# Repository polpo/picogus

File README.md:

# PicoGUS

ISA sound card and CD-ROM drive emulation on the Raspberry Pi Pico's RP2040 microcontroller. PicoGUS can emulate:

* [Gravis Ultrasound (GUS)](https://en.wikipedia.org/wiki/Gravis_Ultrasound) - the primary focus of PicoGUS, hence the name
* [Sound Blaster 16](https://en.wikipedia.org/wiki/Sound_Blaster_16) (OPL3) / [Sound Blaster Pro 2](https://en.wikipedia.org/wiki/Sound_Blaster#Sound_Blaster_Pro_2,_CT1600) (OPL3) / [AdLib](https://en.wikipedia.org/wiki/Ad_Lib,_Inc.) (OPL2)
* [MPU-401 (with intelligent mode)](https://en.wikipedia.org/wiki/MPU-401) - outputs MIDI data on 3.5mm MIDI TRS connector
* [Tandy 3-voice](http://www.vgmpf.com/Wiki/index.php?title=Tandy_3_Voice)
* [CMS/Game Blaster](http://nerdlypleasures.blogspot.com/2012/10/all-you-ever-wanted-to-know-about.html)
* [Game port joystick](https://en.wikipedia.org/wiki/Game_port)
* [Panasonic/MKE CD-ROM](https://en.wikipedia.org/wiki/Panasonic_CD_interface)
* USB drive access from DOS: the drive plugged into the PicoGUS mapped to a DOS drive letter with `PGUSDFS.EXE` (see [pgusdfs/README.md](pgusdfs/README.md))

Current status: perpetual beta! See the [main wiki page](https://github.com/polpo/picogus/wiki) for current status and the [compatibility list](https://github.com/polpo/picogus/wiki/Compatibility-list) for support status of various DOS programs and other system compatibility notes. This project has a heavy demoscene focus due to the GUS's history so that's what I've concentrated on, but GUS support in games is very good to excellent.

Want to buy a PicoGUS? Fully assembled PicoGUS 2.0 sound cards are available from these sources, all of whom ship worldwide:

* [Joe's Computer Museum Shop](https://jcm-1.com/product/picogus-v2/) - in US 🇺🇸
* [Serdashop](https://www.serdashop.com/PicoGUS) - in EU 🇪🇺
* [Flamelily IT](https://shop.flamelily.co.uk/picogus) - in UK 🇬🇧

Want to make your own PicoGUS? See the [build guide](https://github.com/polpo/picogus/wiki/Building-your-PicoGUS). Note that the more DIY friendly v1.1.1 hardware has some documented issues with reset – a forthcoming v1.2 revision will fix these issues. **Important caveat**: due to the specs of the Pico, assumptions made by programs written to use the GUS, the imprecise nature of emulation, and the varying specs of retro DOS PC hardware, some things will likely never be perfect. **This is still a work in progress.**

Have a PicoGUS and want to use it? See the [configuring and using your PicoGUS guide](https://github.com/polpo/picogus/wiki/Configuring-and-using-your-PicoGUS).

Want to support PicoGUS? I have a limited number of machines to test PicoGUS in and donating either money or motherboards would be greatly appreciated and help increase the compatibility of PicoGUS.

You can donate via [PayPal](https://paypal.me/ianpolpo) or Ko-Fi: 

See/hear PicoGUS in action on YouTube:

Videos by others:

My videos:

## Open Source Credits

* [Raspberry Pi Pico C/C++ SDK](https://github.com/raspberrypi/pico-sdk)
* `pico_audio_i2s` from [pico-extras](https://github.com/raspberrypi/pico-extras)
* `stdio_async_uart` from [PicoCart64](https://github.com/kbeckmann/PicoCart64)
* `gus-x.cpp` adapted from [DOSBox-X](https://github.com/joncampbell123/dosbox-x)
* OPL/AdLib emulation from [rp2040-doom](https://github.com/kilograham/rp2040-doom) (based on [emu8950](https://github.com/digital-sound-antiques/emu8950))
* MPU-401 emulation adapted from [HardMPU](https://github.com/ab0tj/HardMPU) and [DOSBox-X](https://github.com/joncampbell123/dosbox-x)
* Tandy 3-voice emulation based on code contributed by [Aaron Giles](https://aarongiles.com/), adapted from [DREAMM](https://aarongiles.com/dreamm/) 
* CMS emulation based on code contributed by [Aaron Giles](https://aarongiles.com/), adapted from [DREAMM](https://aarongiles.com/dreamm/)
* USB support uses [TinyUSB](https://github.com/hathach/tinyusb) and [tusb_xinput](https://github.com/Ryzee119/tusb_xinput) with USB mass storage improvements by rppicomidi and wbcbz7.
* FAT drive support by [FatFS](https://elm-chan.org/fsw/ff/)

## License

The hardware portions of this repository (hw/ directory) are licensed under the CERN OHL version 2, permissive.

The software portions of this repository (sw/, pgusinit/ directories) as a collection are licensed under the GNU GPL version 2. Some files are individually dual-licensed under BSD or MIT licenses – see the license in the file headers for details.

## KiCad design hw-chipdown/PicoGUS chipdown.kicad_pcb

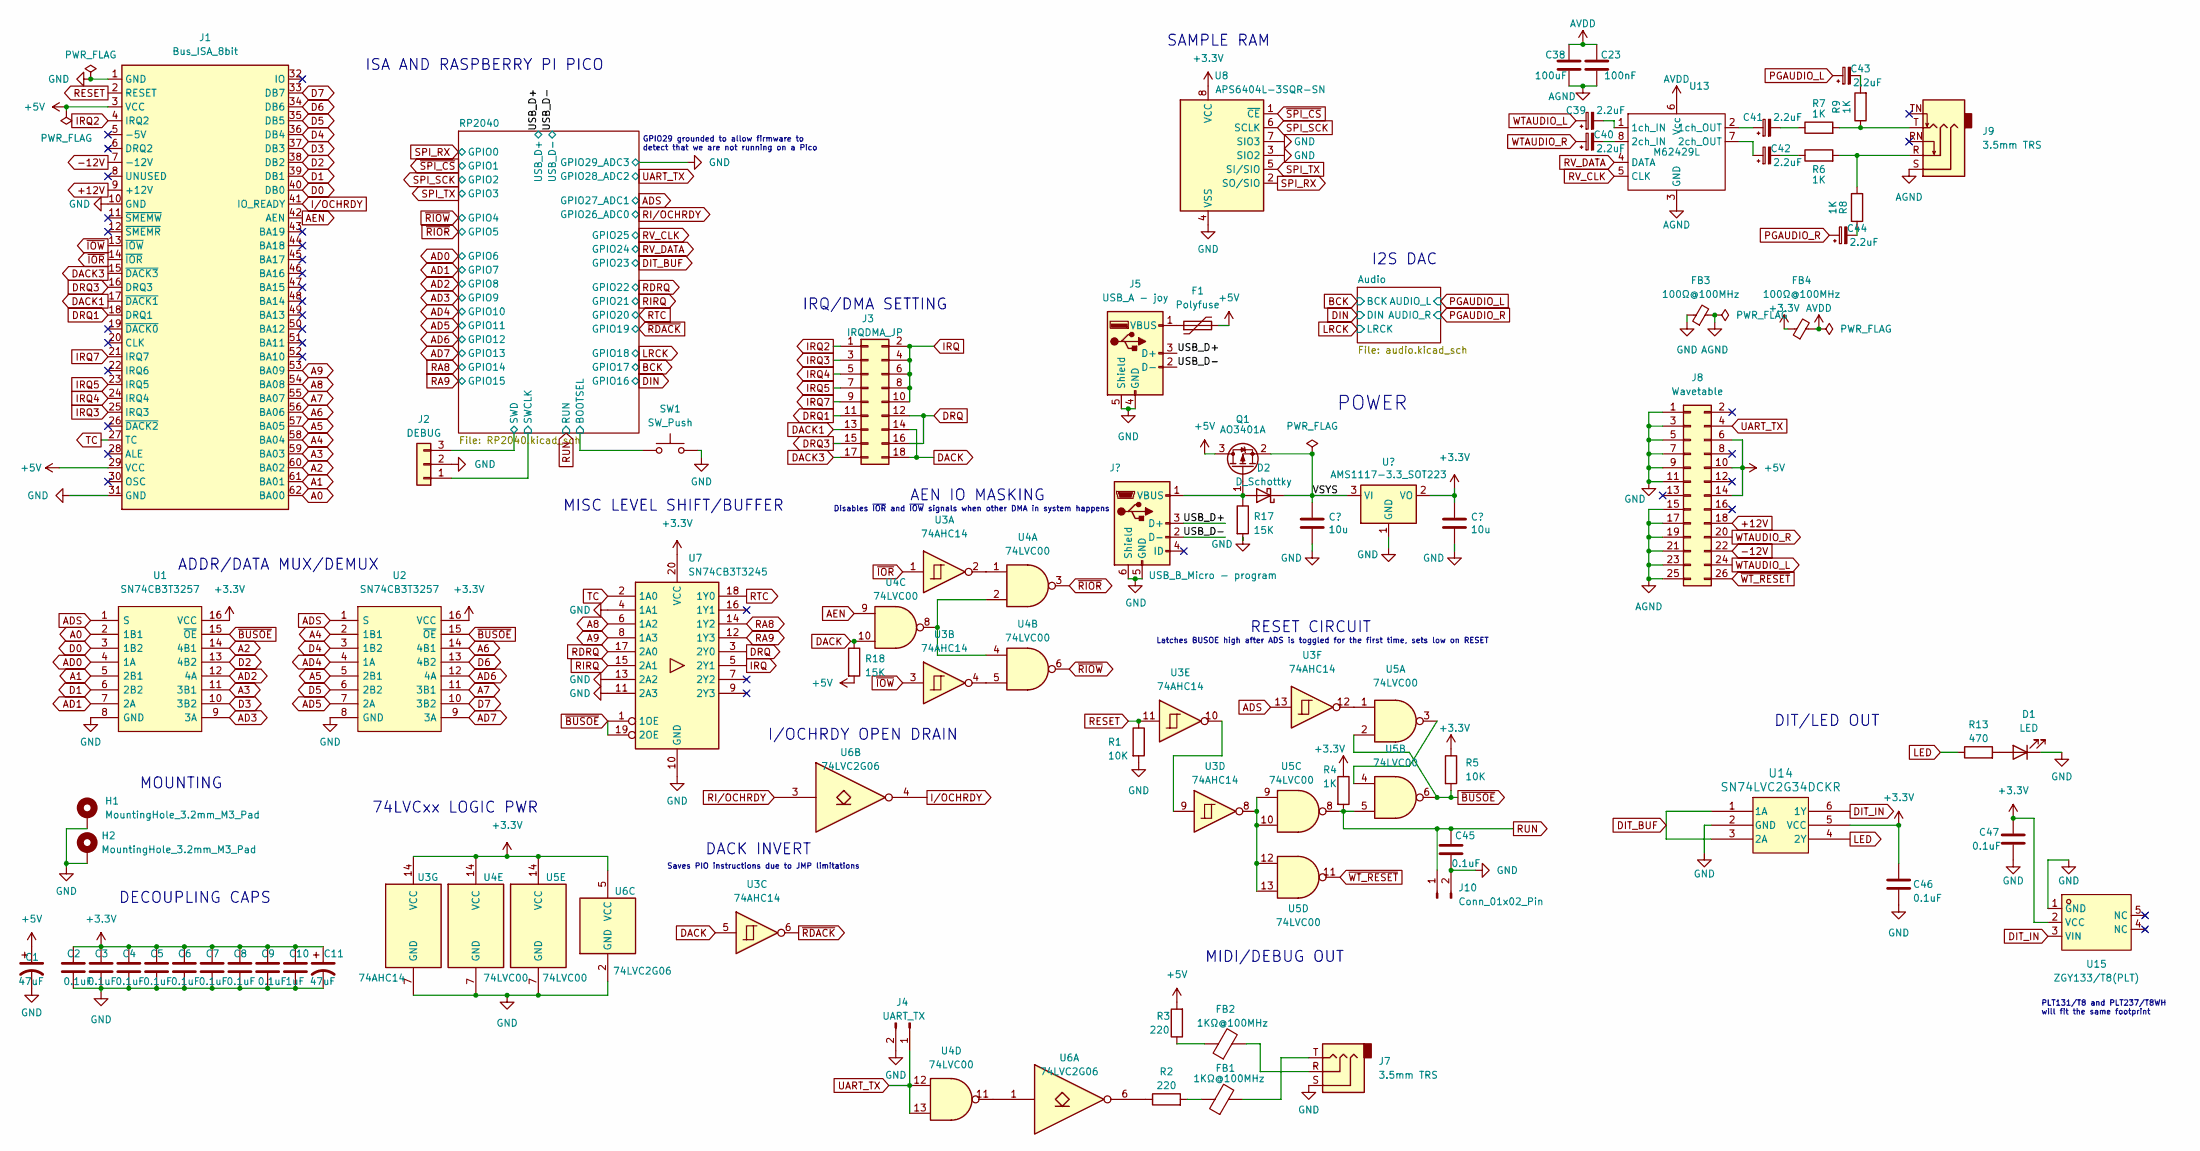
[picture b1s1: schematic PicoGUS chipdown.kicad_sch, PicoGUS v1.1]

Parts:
C1, C11: 47uF; C_1206_3216Metric
C2, C3, C4, C5, C6, C7, C8, C9, C45, C46, C47: 0.1uF; C_0402_1005Metric
C10: 1uF; C_0603_1608Metric
C12, C13: 10u; C_0805_2012Metric
C23: 100nF; C_0402_1005Metric
C38: 100uF; C_1206_3216Metric
C39, C40, C41, C42, C43, C44: 2.2uF; CP_Elec_4x5.4
D1: LED; LED_0603_1608Metric
D2: D_Schottky; D_SOD-323_HandSoldering
F1: Polyfuse; Fuse_1206_3216Metric
FB1, FB2: 1KΩ@100MHz; L_0805_2012Metric
FB3, FB4: 100Ω@100MHz; L_0805_2012Metric
H1, H2: MountingHole_3.2mm_M3_Pad
J1: Bus_ISA_8bit; BUS_PC_chamfer
J2: DEBUG; JST_SH_BM03B-SRSS-TB_1x03-1MP_P1.00mm_Vertical
J3: IRQDMA_JP; PinHeader_2x09_P2.54mm_Vertical
J4: UART_TX; PinHeader_1x02_P2.54mm_Vertical
J5: USB_A - joy; USB-A_902-131A1011D10100
J6: USB_B_Micro - program; USB-microB_U254-051T-4BH83-F1S
J7, J9: 3.5mm TRS; Jack_3.5mm_CUI_SJ1-3535NG_Horizontal
J8: Wavetable
J10: Conn_01x02_Pin; PinHeader_1x02_P2.54mm_Vertical
Q1: AO3401A; SOT-23
R1, R5: 10K; R_0402_1005Metric
R2, R3: 220; R_0805_2012Metric
R4, R6, R7, R8, R9: 1K; R_0402_1005Metric
R13: 470; R_0402_1005Metric
R17, R18: 15K; R_0402_1005Metric
SW1: SW_Push; SW_SPST_TL3305A
U1, U2: SN74CB3T3257; TSSOP-16_4.4x5mm_P0.65mm; Manufacturer_Part_Number 74FST3257DR2G; Mouser Part Number 863-74FST3257DR2G
U3: 74AHC14; TSSOP-14_4.4x5mm_P0.65mm
U4, U5: 74LVC00; TSSOP-14_4.4x5mm_P0.65mm
U6: 74LVC2G06; SOT-363_SC-70-6
U7: SN74CB3T3245; TSSOP-20_4.4x6.5mm_P0.65mm
U8: APS6404L-3SQR-SN; SOIC-8_3.9x4.9mm_P1.27mm
U9: AMS1117-3.3_SOT223; SOT-223-3_TabPin2
U13: M62429L; SOIC-8_3.9x4.9mm_P1.27mm
U14: SN74LVC2G34DCKR; SOT-363_SC-70-6
U15: ZGY133/T8(PLT); OPTO-TH_ZGY133-T8-PLT; LCSC Part C277780

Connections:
+5V: C1.1, F1.2, J1.3 (VCC), J1.29 (VCC), J8.6, J8.10, J8.14, Q1.3 (D), R3.2, R18.2
+12V: J1.9 (+12V), J8.18
-12V: J1.7 (-12V), J8.22
/RP2040/SWCLK: J2.1; also elsewhere on the board
/RP2040/SWD: J2.3; also elsewhere on the board
/RP2040/~USB_BOOT: SW1.1; also elsewhere on the board
/USB_D+: J5.3 (D+), J6.3 (D+); also elsewhere on the board
/USB_D-: J5.2 (D-), J6.2 (D-); also elsewhere on the board
/VSYS: C12.1, D2.1 (K), Q1.2 (S), U9.3 (VI)
A0: J1.62 (BA00), U1.2 (1B1)
A1: J1.61 (BA01), U1.5 (2B1)
A2: J1.60 (BA02), U1.14 (4B1)
A3: J1.59 (BA03), U1.11 (3B1)
A4: J1.58 (BA04), U2.2 (1B1)
A5: J1.57 (BA05), U2.5 (2B1)
A6: J1.56 (BA06), U2.14 (4B1)
A7: J1.55 (BA07), U2.11 (3B1)
A8: J1.54 (BA08), U7.6 (1A2)
A9: J1.53 (BA09), U7.8 (1A3)
AD0: U1.4 (1A); also elsewhere on the board
AD1: U1.7 (2A); also elsewhere on the board
AD2: U1.12 (4A); also elsewhere on the board
AD3: U1.9 (3A); also elsewhere on the board
AD4: U2.4 (1A); also elsewhere on the board
AD5: U2.7 (2A); also elsewhere on the board
AD6: U2.12 (4A); also elsewhere on the board
AD7: U2.9 (3A); also elsewhere on the board
ADS: U1.1 (S), U2.1 (S), U3.13; also elsewhere on the board
AEN: J1.42 (AEN), U4.9
AGND: C23.2, C38.2, FB3.2, J8.15, J8.17, J8.19, J8.21, J8.23, J8.25, J9.S, U13.3 (GND); also elsewhere on the board
D0: J1.40 (DB0), U1.3 (1B2)
D1: J1.39 (DB1), U1.6 (2B2)
D2: J1.38 (DB2), U1.13 (4B2)
D3: J1.37 (DB3), U1.10 (3B2)
D4: J1.36 (DB4), U2.3 (1B2)
D5: J1.35 (DB5), U2.6 (2B2)
D6: J1.34 (DB6), U2.13 (4B2)
D7: J1.33 (DB7), U2.10 (3B2)
DACK: J3.14, J3.18, R18.1, U3.5, U4.10
DACK1: J1.17 (~DACK1), J3.13
DACK3: J1.15 (~DACK3), J3.17
DIT_BUF: U14.1 (1A), U14.3 (2A); also elsewhere on the board
DIT_IN: U14.6 (1Y), U15.3 (VIN)
DRQ: J3.12, J3.16, U7.3 (2Y0)
DRQ1: J1.18 (DRQ1), J3.11
DRQ3: J1.16 (DRQ3), J3.15
GND: C1.2, C2.2, C3.2, C4.2, C5.2, C6.2, C7.2, C8.2, C9.2, C10.2, C11.2, C12.2, C13.2, C45.2, C46.2, C47.2, D1.1 (K), FB3.1, H1.1, H2.1, J1.1 (GND), J1.10 (GND), J1.31 (GND), J2.2, J4.2, J5.4 (GND), J5.5 (Shield), J6.5 (GND), J6.6 (Shield), J7.S, J8.1, J8.3, J8.5, J8.7, J8.9, J8.11, J10.2, R1.2, R17.2, SW1.2, U1.8 (GND), U2.8 (GND), U3.7 (GND), U4.7 (GND), U5.7 (GND), U6.2 (GND), U7.4 (1A1), U7.10 (GND), U7.11 (2A3), U7.13 (2A2), U8.3 (SIO2), U8.4 (VSS), U8.7 (SIO3), U9.1 (GND), U14.2 (GND), U15.1 (GND); also elsewhere on the board
IRQ: J3.2, J3.4, J3.6, J3.8, J3.10, U7.5 (2Y1)
IRQ2: J1.4 (IRQ2), J3.1
IRQ3: J1.25 (IRQ3), J3.3
IRQ4: J1.24 (IRQ4), J3.5
IRQ5: J1.23 (IRQ5), J3.7
IRQ7: J1.21 (IRQ7), J3.9
I/OCHRDY: J1.41 (IO_READY), U6.4
LED: R13.1, U14.4 (2Y)
unnamed: C41.2, R7.1
unnamed: C42.2, R6.1
unnamed: C43.2, R9.2
unnamed: C44.2, R8.2
unnamed: D1.2 (A), R13.2
unnamed: D2.2 (A), J6.1 (VBUS), Q1.1 (G), R17.1
unnamed: FB1.1, R2.2
unnamed: FB1.2, J7.T
unnamed: FB2.1, R3.1
unnamed: FB2.2, J7.R
unnamed: F1.1, J5.1 (VBUS)
unnamed: J9.R, R6.2, R8.1
unnamed: J9.T, R7.2, R9.1
unnamed: R2.1, U6.6
unnamed: U3.2, U4.1
unnamed: U3.4, U4.5
unnamed: U3.8, U5.9, U5.10, U5.12, U5.13
unnamed: U3.9, U3.10
unnamed: U3.12, U5.1
unnamed: U4.2, U4.4, U4.8
unnamed: U4.11, U6.1
unnamed: U5.3, U5.4
unnamed: C39.2, U13.1 (1ch_IN)
unnamed: C41.1, U13.2 (1ch_OUT)
unnamed: C40.2, U13.8 (2ch_IN)
unnamed: C42.1, U13.7 (2ch_OUT)
PGAUDIO_L: C43.1; also elsewhere on the board
PGAUDIO_R: C44.1; also elsewhere on the board
RA8: U7.14 (1Y2); also elsewhere on the board
RA9: U7.12 (1Y3); also elsewhere on the board
RDRQ: U7.17 (2A0); also elsewhere on the board
RESET: J1.2 (RESET), R1.1, U3.11
RIRQ: U7.15 (2A1); also elsewhere on the board
RI/OCHRDY: U6.3; also elsewhere on the board
RTC: U7.18 (1Y0); also elsewhere on the board
RUN: C45.1, J10.1, R4.2, U5.5, U5.8; also elsewhere on the board
RV_CLK: U13.5 (CLK); also elsewhere on the board
RV_DATA: U13.4 (DATA); also elsewhere on the board
SPI_RX: U8.2 (SO/SIO); also elsewhere on the board
SPI_SCK: U8.6 (SCLK); also elsewhere on the board
SPI_TX: U8.5 (SI/SIO); also elsewhere on the board
TC: J1.27 (TC), U7.2 (1A0)
UART_TX: J4.1, J8.4, U4.12, U4.13; also elsewhere on the board
WTAUDIO_L: C39.1, J8.24
WTAUDIO_R: C40.1, J8.20
~BUSOE: R5.2, U1.15 (~OE), U2.15 (~OE), U5.2, U5.6, U7.1 (1OE), U7.19 (2OE)
~IOR: J1.14 (~IOR), U3.1
~IOW: J1.13 (~IOW), U3.3
~RDACK: U3.6; also elsewhere on the board
~RIOR: U4.3; also elsewhere on the board
~RIOW: U4.6; also elsewhere on the board
~SPI_CS: U8.1 (~CE); also elsewhere on the board
~WT_RESET: J8.26, U5.11

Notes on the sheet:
Saves PIO instructions due to JMP limitations
DECOUPLING CAPS
GPIO29 grounded to allow firmware to detect that we are not running on a Pico
I2S DAC
Disables ~{IOR} and ~{IOW} signals when other DMA in system happens
Latches BUSOE high after ADS is toggled for the first time, sets low on RESET
MIDI/DEBUG OUT
MOUNTING
MISC LEVEL SHIFT/BUFFER
IRQ/DMA SETTING
DIT/LED OUT
DACK INVERT
ADDR/DATA MUX/DEMUX
SAMPLE RAM
PLT131/T8 and PLT237/T8WH will fit the same footprint
AEN IO MASKING
ISA AND RASPBERRY PI PICO
POWER
RESET CIRCUIT
I/OCHRDY OPEN DRAIN
74LVCxx LOGIC PWR

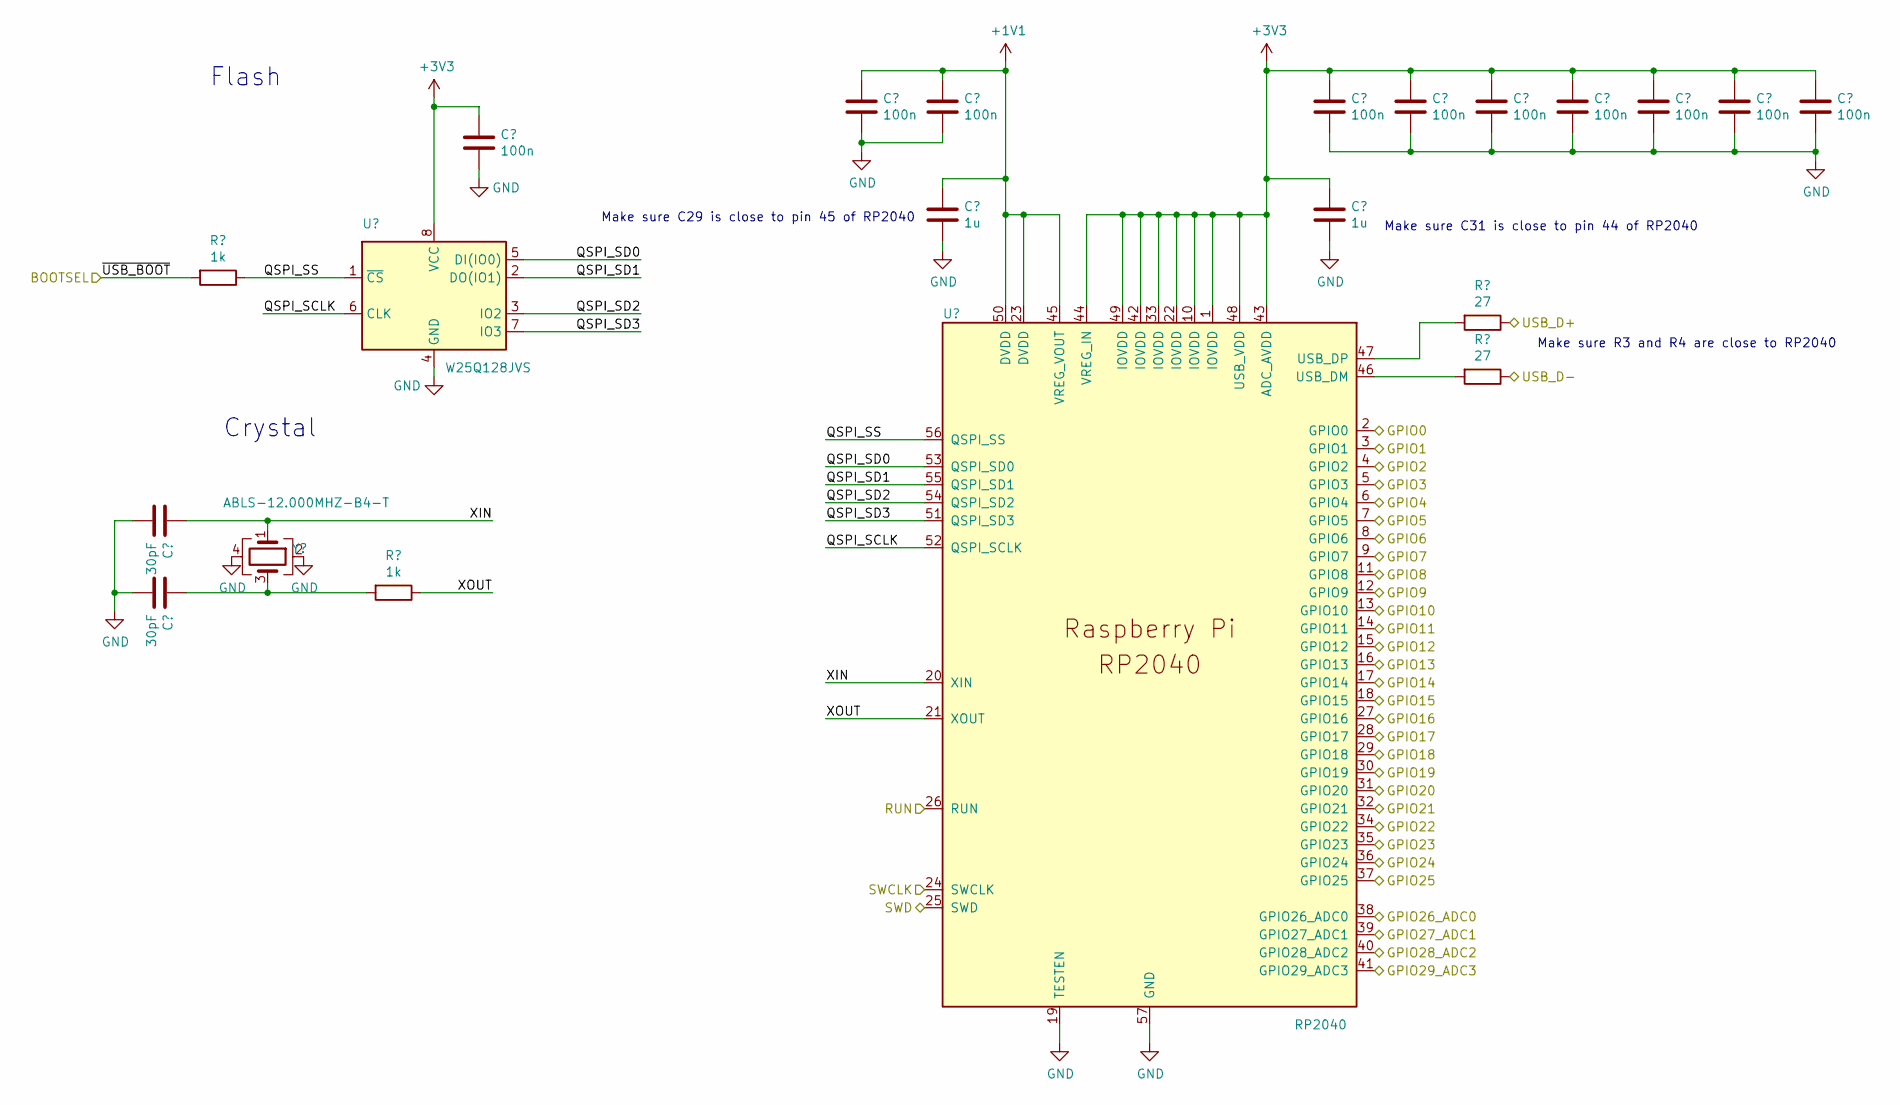
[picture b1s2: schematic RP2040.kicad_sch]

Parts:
C24, C25: 30pF; C_0402_1005Metric
C26, C27, C28, C30, C32, C33, C34, C35, C36, C37: 100n; C_0402_1005Metric
C29, C31: 1u; C_0402_1005Metric
R12, R14: 1k; C_0402_1005Metric
R15, R16: 27; C_0402_1005Metric
U11: W25Q128JVS; SOIC-8_5.23x5.23mm_P1.27mm
U12: RP2040; QFN-56-1EP_7x7mm_P0.4mm_EP3.2x3.2mm_ThermalVias
Y1: ABLS-12.000MHZ-B4-T; Crystal_SMD_3225-4Pin_3.2x2.5mm

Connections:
+1V1: C27.1, C28.1, C29.1, U12.23 (DVDD), U12.45 (VREG_VOUT), U12.50 (DVDD)
/RP2040/QSPI_SCLK: U11.6 (CLK), U12.52 (QSPI_SCLK)
/RP2040/QSPI_SD0: U11.5 (DI(IO0)), U12.53 (QSPI_SD0)
/RP2040/QSPI_SD1: U11.2 (DO(IO1)), U12.55 (QSPI_SD1)
/RP2040/QSPI_SD2: U11.3 (IO2), U12.54 (QSPI_SD2)
/RP2040/QSPI_SD3: U11.7 (IO3), U12.51 (QSPI_SD3)
/RP2040/QSPI_SS: R12.1, U11.1 (~CS), U12.56 (QSPI_SS)
/RP2040/SWCLK: U12.24 (SWCLK); also elsewhere on the board
/RP2040/SWD: U12.25 (SWD); also elsewhere on the board
/RP2040/XIN: C24.1, U12.20 (XIN), Y1.1
/RP2040/XOUT: R14.1, U12.21 (XOUT)
/RP2040/~USB_BOOT: R12.2; also elsewhere on the board
/USB_D+: R15.1; also elsewhere on the board
/USB_D-: R16.1; also elsewhere on the board
AD0: U12.8 (GPIO6); also elsewhere on the board
AD1: U12.9 (GPIO7); also elsewhere on the board
AD2: U12.11 (GPIO8); also elsewhere on the board
AD3: U12.12 (GPIO9); also elsewhere on the board
AD4: U12.13 (GPIO10); also elsewhere on the board
AD5: U12.14 (GPIO11); also elsewhere on the board
AD6: U12.15 (GPIO12); also elsewhere on the board
AD7: U12.16 (GPIO13); also elsewhere on the board
ADS: U12.39 (GPIO27_ADC1); also elsewhere on the board
BCK: U12.28 (GPIO17); also elsewhere on the board
DIN: U12.27 (GPIO16); also elsewhere on the board
DIT_BUF: U12.35 (GPIO23); also elsewhere on the board
GND: C24.2, C25.2, C26.2, C27.2, C28.2, C29.2, C30.2, C31.2, C32.2, C33.2, C34.2, C35.2, C36.2, C37.2, U11.4 (GND), U12.19 (TESTEN), U12.41 (GPIO29_ADC3), U12.57 (GND), Y1.2, Y1.4; also elsewhere on the board
LRCK: U12.29 (GPIO18); also elsewhere on the board
unnamed: C25.1, R14.2, Y1.3
unnamed: R16.2, U12.46 (USB_DM)
unnamed: R15.2, U12.47 (USB_DP)
RA8: U12.17 (GPIO14); also elsewhere on the board
RA9: U12.18 (GPIO15); also elsewhere on the board
RDRQ: U12.34 (GPIO22); also elsewhere on the board
RIRQ: U12.32 (GPIO21); also elsewhere on the board
RI/OCHRDY: U12.38 (GPIO26_ADC0); also elsewhere on the board
RTC: U12.31 (GPIO20); also elsewhere on the board
RUN: U12.26 (RUN); also elsewhere on the board
RV_CLK: U12.37 (GPIO25); also elsewhere on the board
RV_DATA: U12.36 (GPIO24); also elsewhere on the board
SPI_RX: U12.2 (GPIO0); also elsewhere on the board
SPI_SCK: U12.4 (GPIO2); also elsewhere on the board
SPI_TX: U12.5 (GPIO3); also elsewhere on the board
UART_TX: U12.40 (GPIO28_ADC2); also elsewhere on the board
~RDACK: U12.30 (GPIO19); also elsewhere on the board
~RIOR: U12.7 (GPIO5); also elsewhere on the board
~RIOW: U12.6 (GPIO4); also elsewhere on the board
~SPI_CS: U12.3 (GPIO1); also elsewhere on the board

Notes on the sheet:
Make sure R3 and R4 are close to RP2040
Make sure C29 is close to pin 45 of RP2040
Make sure C31 is close to pin 44 of RP2040
Flash
Crystal

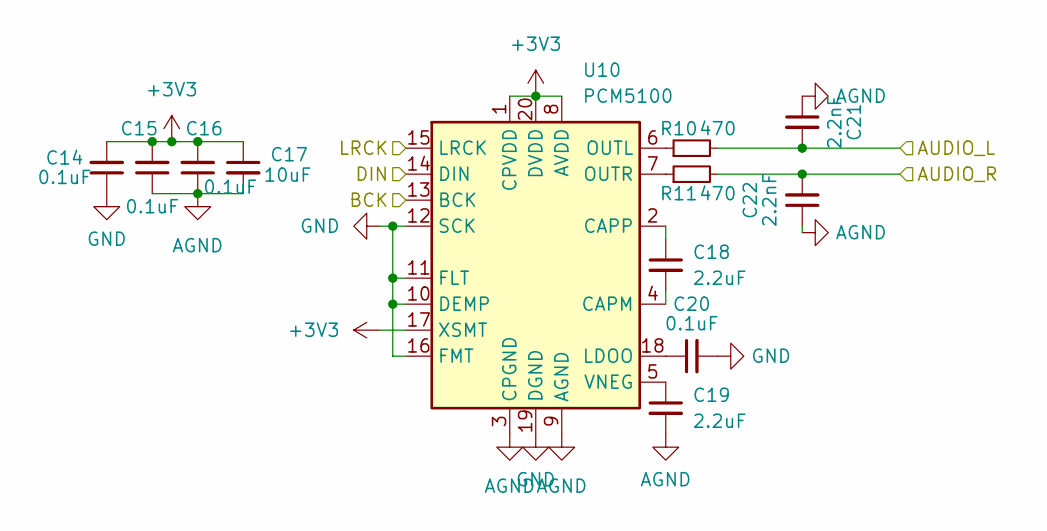
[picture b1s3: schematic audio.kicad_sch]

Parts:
C14, C15, C16, C20: 0.1uF; C_0402_1005Metric
C17: 10uF; C_0805_2012Metric
C18, C19: 2.2uF; C_0402_1005Metric
C21, C22: 2.2nF; C_0603_1608Metric
R10, R11: 470; R_0402_1005Metric
U10: PCM5100; TSSOP-20_4.4x6.5mm_P0.65mm

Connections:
AGND: C15.1, C16.1, C17.2, C19.2, C21.1, C22.1, U10.3 (CPGND), U10.9 (AGND); also elsewhere on the board
BCK: U10.13 (BCK); also elsewhere on the board
DIN: U10.14 (DIN); also elsewhere on the board
GND: C14.1, C20.2, U10.10 (DEMP), U10.11 (FLT), U10.12 (SCK), U10.16 (FMT), U10.19 (DGND); also elsewhere on the board
LRCK: U10.15 (LRCK); also elsewhere on the board
unnamed: C18.2, U10.4 (CAPM)
unnamed: C18.1, U10.2 (CAPP)
unnamed: C20.1, U10.18 (LDOO)
unnamed: R10.1, U10.6 (OUTL)
unnamed: R11.1, U10.7 (OUTR)
unnamed: C19.1, U10.5 (VNEG)
PGAUDIO_L: C21.2, R10.2; also elsewhere on the board
PGAUDIO_R: C22.2, R11.2; also elsewhere on the board

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
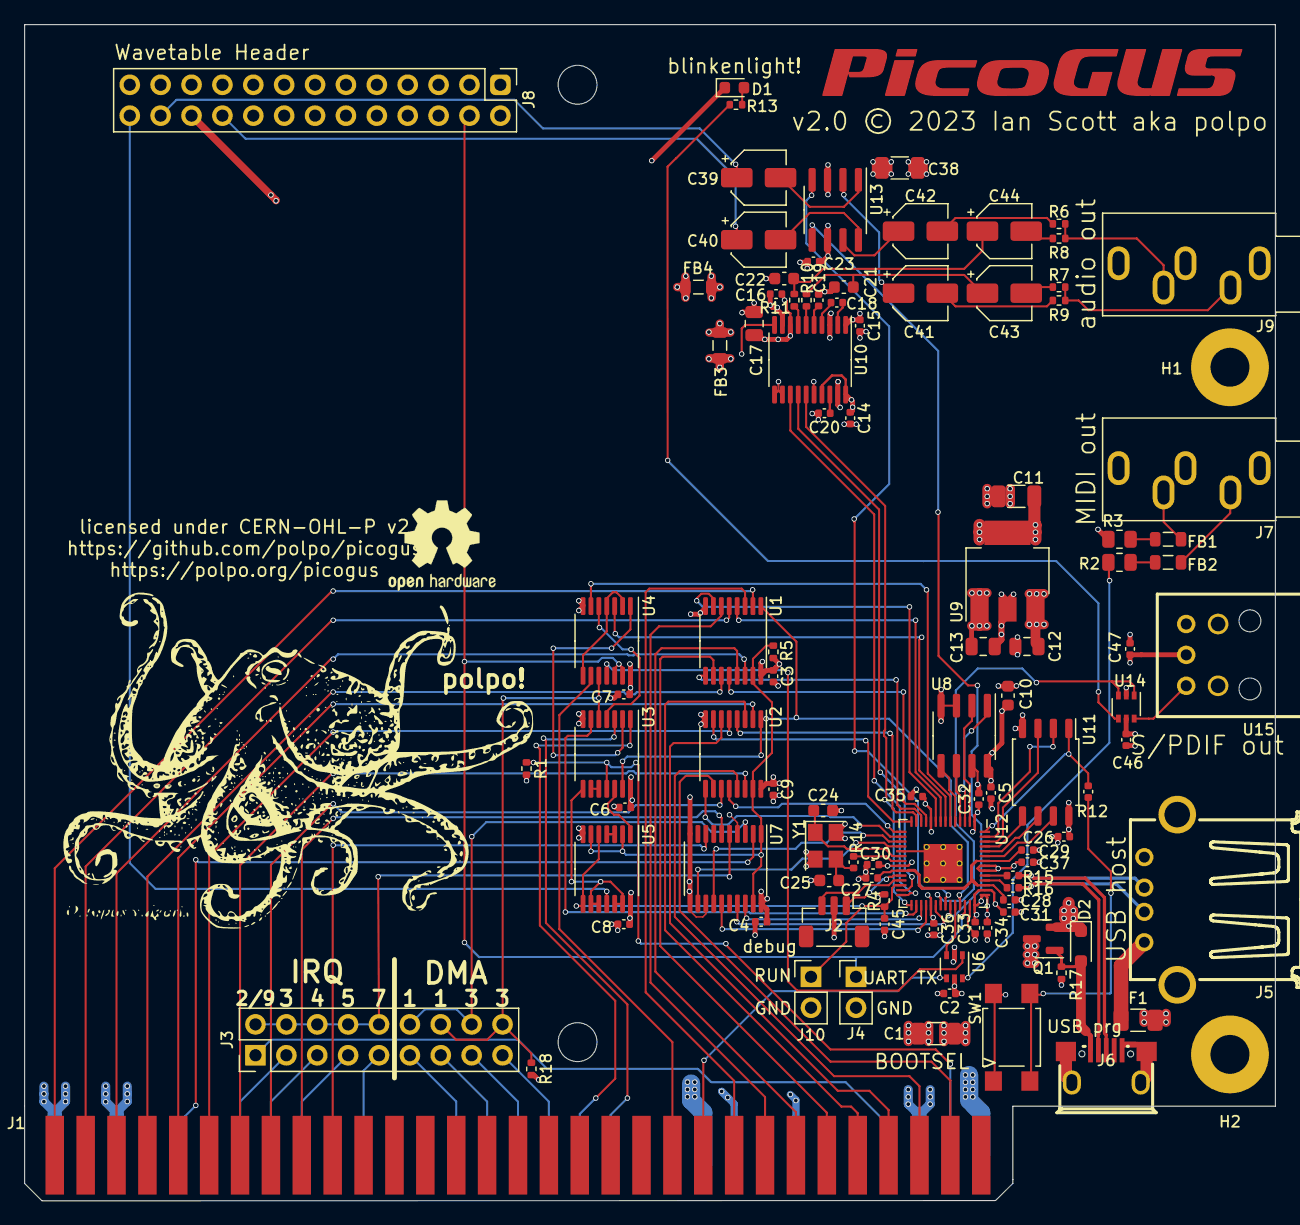
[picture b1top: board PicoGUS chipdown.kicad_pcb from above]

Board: 4 copper layers, 102.9 x 96.7 mm, 102 parts (0 on the bottom side), 131 nets.

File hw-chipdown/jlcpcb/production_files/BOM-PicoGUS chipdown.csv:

Comment,Designator,Footprint,LCSC
100Ω@100MHz,"FB3,FB4",L_0805_2012Metric,C1015
1k,"R12,R14,R4,R6,R7,R8,R9",C_0402_1005Metric,C11702
2.2uF,"C18,C19",C_0402_1005Metric,C12530
PCM5100,U10,TSSOP-20_4.4x6.5mm_P0.65mm,C131154
SN74LVC2G34DCKR,U14,SOT-363_SC-70-6,C14461
AO3401A,Q1,SOT-23,C15127
0.1uF,"C14,C15,C16,C2,C20,C23,C26,C27,C28,C3,C30,C32,C33,C34,C35,C36,C37,C4,C45,C46,C47,C5,C6,C7,C8,C9",C_0402_1005Metric,C1525
SN74CB3T3245,U7,TSSOP-20_4.4x6.5mm_P0.65mm,C15298
1KΩ@100MHz,"FB1,FB2",L_0805_2012Metric,C155073
1uF,C10,C_0603_1608Metric,C15849
10u,"C12,C13,C17",C_0805_2012Metric,C15850
2.2nF,"C21,C22",C_0603_1608Metric,C1604
30pF,"C24,C25",C_0603_1608Metric,C1658
D_Schottky,D2,D_SOD-323_HandSoldering,C191023
RP2040,U12,QFN-56-1EP_7x7mm_P0.4mm_EP3.2x3.2mm_ThermalVias,C2040
USB_A - joy,J5,USB-A_902-131A1011D10100,C2345
27,"R15,R16",C_0402_1005Metric,C25100
470,"R10,R11,R13",R_0402_1005Metric,C25117
10K,"R1,R5",R_0402_1005Metric,C25744
15K,"R17,R18",R_0402_1005Metric,C25756
APS6404L-3SQR-SN,U8,SOIC-8_3.9x4.9mm_P1.27mm,C261881
ZGY133/T8(PLT),U15,OPTO-TH_ZGY133-T8-PLT,C277780
3.5mm TRS,J7,Jack_3.5mm_CUI_SJ1-3535NG_Horizontal,C2910528
Wavetable,J8,Wavetable,C358701
USB_B_Micro - program,J6,USB-microB_U254-051T-4BH83-F1S,C397452
2.2uF,"C39,C40,C41,C42,C43,C44",CP_Elec_4x5.4,C445039
IRQDMA_JP,J3,PinHeader_2x09_P2.54mm_Vertical,C492426
220,"R2,R3",R_0805_2012Metric,C5120092
1u,"C29,C31",C_0402_1005Metric,C52923
SW_Push,SW1,SW_SPST_TL3305A,C5342982
SN74CB3T3257,"U1,U2",TSSOP-16_4.4x5mm_P0.65mm,C544573
74LVC2G06,U6,SOT-363_SC-70-6,C548560
AMS1117-3.3_SOT223,U9,SOT-223-3_TabPin2,C6186
M62429L,U13,SOIC-8_3.9x4.9mm_P1.27mm,C668666
3.5mm TRS,J9,Jack_3.5mm_CUI_SJ1-3535NG_Horizontal,C692438
LED,D1,LED_0603_1608Metric,C72038
74AHC14,U3,TSSOP-14_4.4x5mm_P0.65mm,C7460
Polyfuse,F1,Fuse_1206_3216Metric,C75464
74LVC00,"U4,U5",TSSOP-14_4.4x5mm_P0.65mm,C7803
W25Q128JVS,U11,SOIC-8_5.23x5.23mm_P1.27mm,C82317
ABLS-12.000MHZ-B4-T,Y1,Crystal_SMD_3225-4Pin_3.2x2.5mm,C9002
47uF,"C1,C11,C38",C_1206_3216Metric,C96123

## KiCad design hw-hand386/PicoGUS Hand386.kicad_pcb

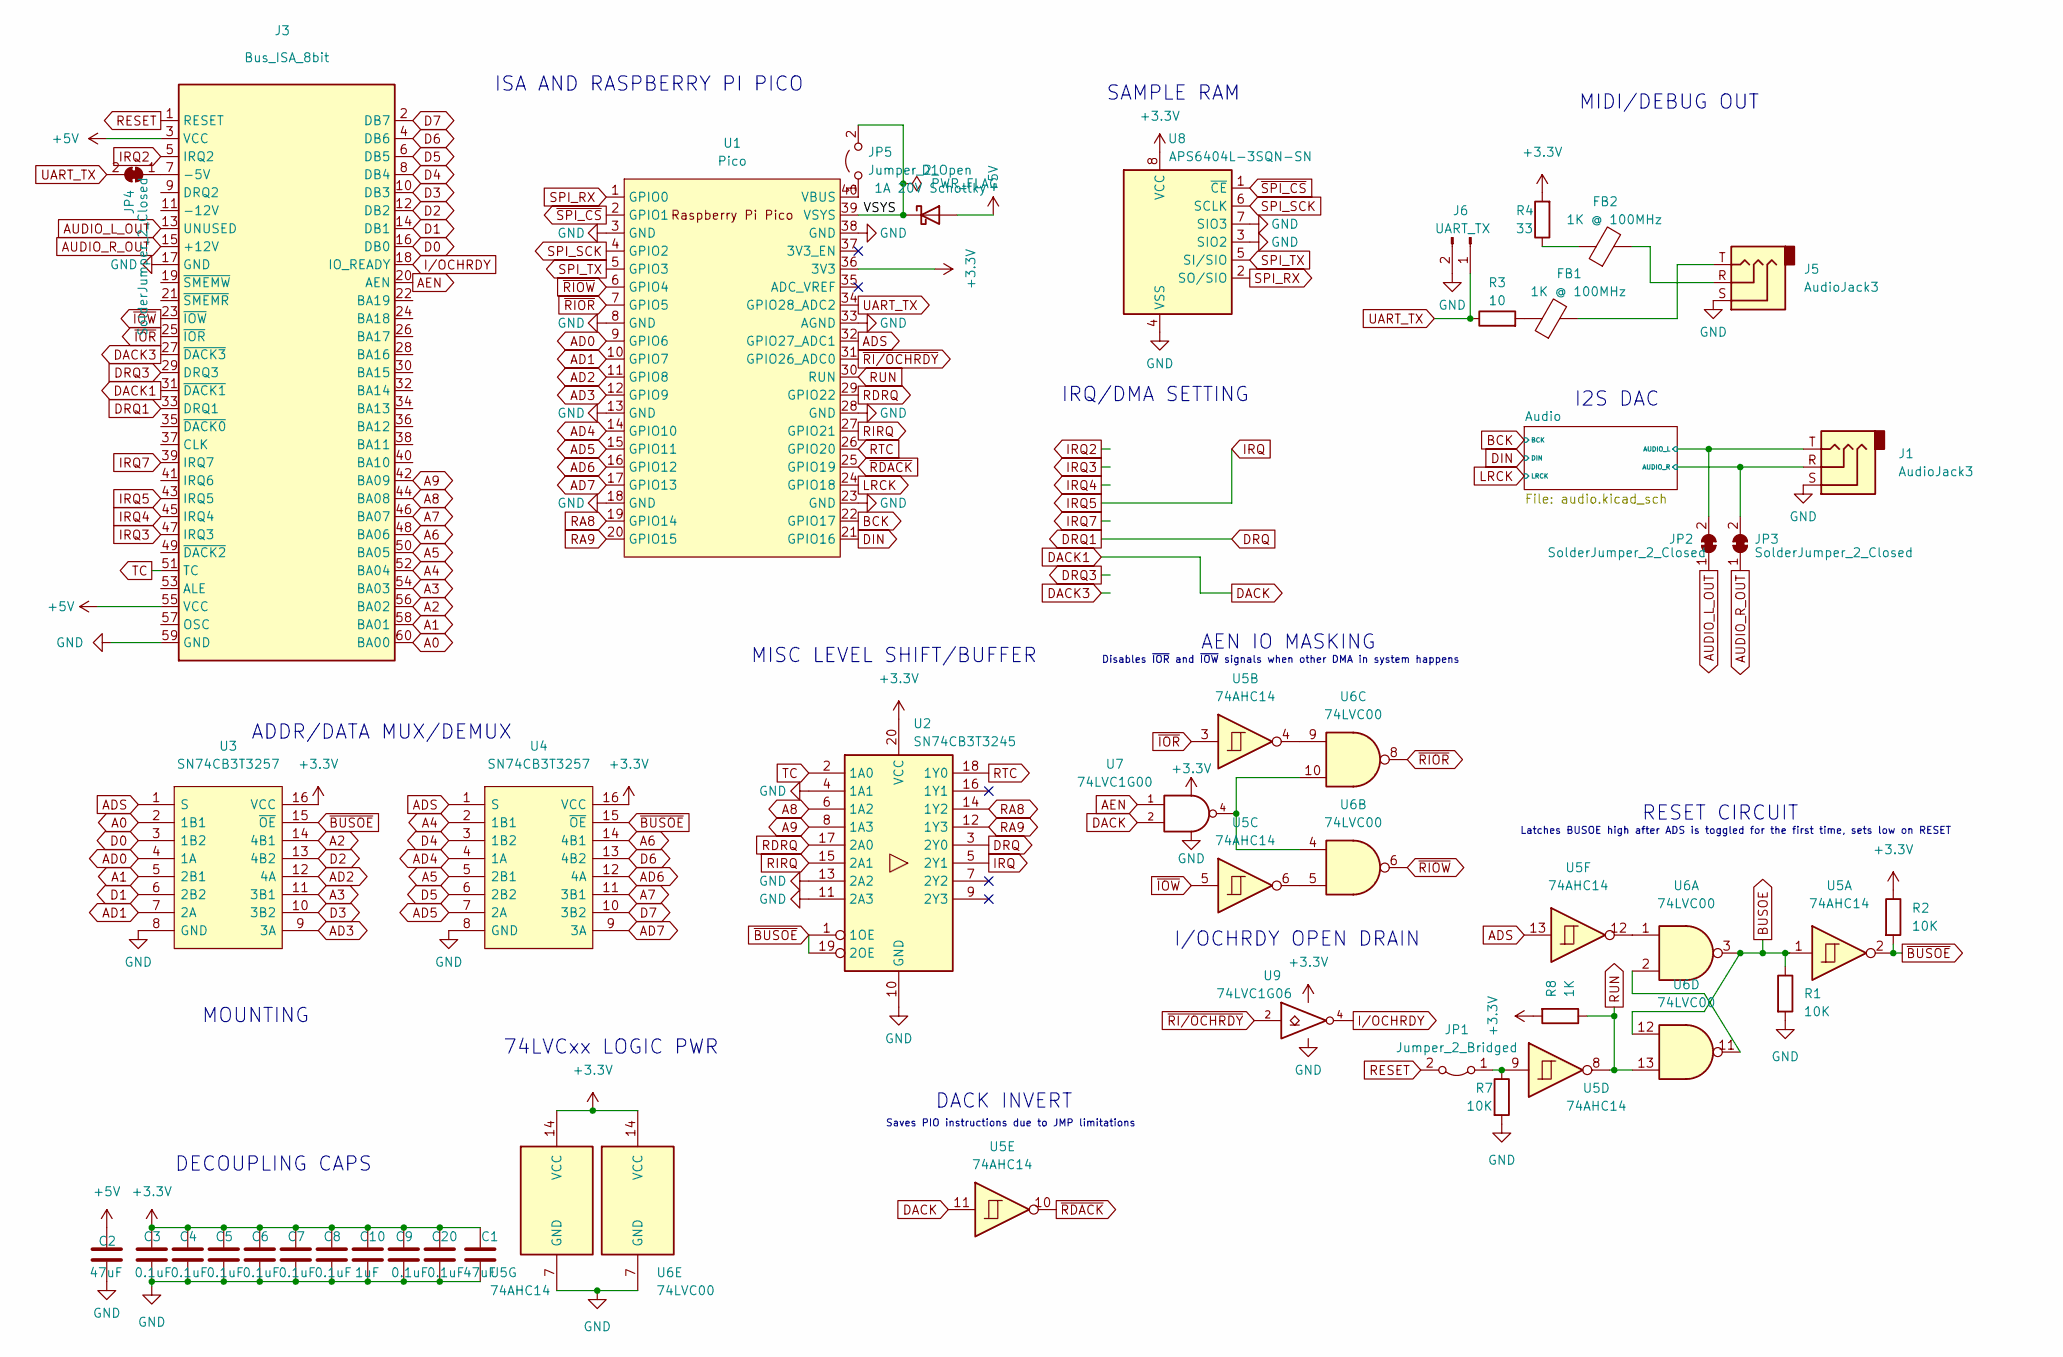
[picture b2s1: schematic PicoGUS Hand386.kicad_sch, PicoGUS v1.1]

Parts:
C1, C2: 47uF; C_1206_3216Metric
C3, C4, C5, C6, C7, C8, C9, C20: 0.1uF; C_0402_1005Metric
C10: 1uF; C_0402_1005Metric
D1: 1A 20V Schottky; D_SOD-123
FB1, FB2: 1K @ 100MHz; L_0603_1608Metric
J1: AudioJack3; PJ-321A
J3: Bus_ISA_8bit; EDGE-60
J5: AudioJack3; PJ-231F-4A
J6: UART_TX; PinHeader_1x02_P2.54mm_Vertical
JP1: Jumper_2_Bridged; PinHeader_1x02_P2.54mm_Vertical
JP2, JP3, JP4: SolderJumper_2_Closed; SolderJumper-2_P1.3mm_Bridged_RoundedPad1.0x1.5mm-nomask
JP5: Jumper_2_Open; PinHeader_1x02_P2.54mm_Vertical
R1, R2, R7: 10K; R_0402_1005Metric
R3: 10; R_0805_2012Metric
R4: 33; R_0805_2012Metric
R8: 1K; R_0402_1005Metric
U1: Pico; RPi_Pico_SMD_TH
U2: SN74CB3T3245; TSSOP-20_4.4x6.5mm_P0.65mm
U3, U4: SN74CB3T3257; TSSOP-16_4.4x5mm_P0.65mm; Manufacturer_Part_Number 74FST3257DR2G; Mouser Part Number 863-74FST3257DR2G
U5: 74AHC14; TSSOP-14_4.4x5mm_P0.65mm
U6: 74LVC00; TSSOP-14_4.4x5mm_P0.65mm
U7: 74LVC1G00; SOT-23-5
U8: APS6404L-3SQN-SN; SOIC-8_3.9x4.9mm_P1.27mm
U9: 74LVC1G06; SOT-23-5

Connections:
+5V: C2.1, D1.2 (A), J3.3 (VCC), J3.55 (VCC)
/Audio/AUDIO_L: J1.T, JP2.2 (B); also elsewhere on the board
/Audio/AUDIO_R: J1.R, JP3.2 (B); also elsewhere on the board
/VSYS: D1.1 (K), JP5.2 (B), U1.39 (VSYS)
A0: J3.60 (BA00), U3.2 (1B1)
A1: J3.58 (BA01), U3.5 (2B1)
A2: J3.56 (BA02), U3.14 (4B1)
A3: J3.54 (BA03), U3.11 (3B1)
A4: J3.52 (BA04), U4.2 (1B1)
A5: J3.50 (BA05), U4.5 (2B1)
A6: J3.48 (BA06), U4.14 (4B1)
A7: J3.46 (BA07), U4.11 (3B1)
A8: J3.44 (BA08), U2.6 (1A2)
A9: J3.42 (BA09), U2.8 (1A3)
AD0: U1.9 (GPIO6), U3.4 (1A)
AD1: U1.10 (GPIO7), U3.7 (2A)
AD2: U1.11 (GPIO8), U3.12 (4A)
AD3: U1.12 (GPIO9), U3.9 (3A)
AD4: U1.14 (GPIO10), U4.4 (1A)
AD5: U1.15 (GPIO11), U4.7 (2A)
AD6: U1.16 (GPIO12), U4.12 (4A)
AD7: U1.17 (GPIO13), U4.9 (3A)
ADS: U1.32 (GPIO27_ADC1), U3.1 (S), U4.1 (S), U5.13
AEN: J3.20 (AEN), U7.1
AUDIO_L_OUT: J3.13 (UNUSED), JP2.1 (A)
AUDIO_R_OUT: J3.15 (+12V), JP3.1 (A)
BCK: U1.22 (GPIO17); also elsewhere on the board
BUSOE: R1.1, U5.1, U6.3, U6.12
D0: J3.16 (DB0), U3.3 (1B2)
D1: J3.14 (DB1), U3.6 (2B2)
D2: J3.12 (DB2), U3.13 (4B2)
D3: J3.10 (DB3), U3.10 (3B2)
D4: J3.8 (DB4), U4.3 (1B2)
D5: J3.6 (DB5), U4.6 (2B2)
D6: J3.4 (DB6), U4.13 (4B2)
D7: J3.2 (DB7), U4.10 (3B2)
DACK: J3.31 (~DACK1), U5.11, U7.2
DACK3: J3.27 (~DACK3)
DIN: U1.21 (GPIO16); also elsewhere on the board
DRQ: J3.33 (DRQ1), U2.3 (2Y0)
DRQ3: J3.29 (DRQ3)
GND: C1.2, C2.2, C3.2, C4.2, C5.2, C6.2, C7.2, C8.2, C9.2, C10.2, C20.2, J1.S, J3.17 (GND), J3.59 (GND), J5.S, J6.2, R1.2, R7.2, U1.3 (GND), U1.8 (GND), U1.13 (GND), U1.18 (GND), U1.23 (GND), U1.28 (GND), U1.33 (AGND), U1.38 (GND), U2.4 (1A1), U2.10 (GND), U2.11 (2A3), U2.13 (2A2), U3.8 (GND), U4.8 (GND), U5.7 (GND), U6.7 (GND), U7.3 (GND), U8.3 (SIO2), U8.4 (VSS), U8.7 (SIO3), U9.3 (GND); also elsewhere on the board
IRQ: J3.43 (IRQ5), U2.5 (2Y1)
IRQ2: J3.5 (IRQ2)
IRQ3: J3.47 (IRQ3)
IRQ4: J3.45 (IRQ4)
IRQ7: J3.39 (IRQ7)
I/OCHRDY: J3.18 (IO_READY), U9.4
LRCK: U1.24 (GPIO18); also elsewhere on the board
unnamed: FB1.1, R3.2
unnamed: FB1.2, J5.T
unnamed: FB2.1, R4.1
unnamed: FB2.2, J5.R
unnamed: J3.7 (-5V), JP4.1 (A)
unnamed: JP1.1 (A), R7.1, U5.9
unnamed: JP5.1 (A), U1.40 (VBUS)
unnamed: U5.4, U6.9
unnamed: U5.6, U6.5
unnamed: U5.12, U6.1
unnamed: U6.4, U6.10, U7.4
unnamed: U6.2, U6.11
RA8: U1.19 (GPIO14), U2.14 (1Y2)
RA9: U1.20 (GPIO15), U2.12 (1Y3)
RDRQ: U1.29 (GPIO22), U2.17 (2A0)
RESET: J3.1 (RESET), JP1.2 (B)
RIRQ: U1.27 (GPIO21), U2.15 (2A1)
RTC: U1.26 (GPIO20), U2.18 (1Y0)
RUN: R8.1, U1.30 (RUN), U5.8, U6.13
SPI_RX: U1.1 (GPIO0), U8.2 (SO/SIO)
SPI_SCK: U1.4 (GPIO2), U8.6 (SCLK)
SPI_TX: U1.5 (GPIO3), U8.5 (SI/SIO)
TC: J3.51 (TC), U2.2 (1A0)
UART_TX: J6.1, JP4.2 (B), R3.1, U1.34 (GPIO28_ADC2)
~BUSOE: R2.2, U2.1 (1OE), U2.19 (2OE), U3.15 (~OE), U4.15 (~OE), U5.2
~IOR: J3.25 (~IOR), U5.3
~IOW: J3.23 (~IOW), U5.5
~RDACK: U1.25 (GPIO19), U5.10
~RIOR: U1.7 (GPIO5), U6.8
~RIOW: U1.6 (GPIO4), U6.6
~RI/OCHRDY: U1.31 (GPIO26_ADC0), U9.2
~SPI_CS: U1.2 (GPIO1), U8.1 (~CE)

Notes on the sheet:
Saves PIO instructions due to JMP limitations
DECOUPLING CAPS
I2S DAC
Disables ~{IOR} and ~{IOW} signals when other DMA in system happens
Latches BUSOE high after ADS is toggled for the first time, sets low on RESET
MIDI/DEBUG OUT
MOUNTING
MISC LEVEL SHIFT/BUFFER
IRQ/DMA SETTING
DACK INVERT
ADDR/DATA MUX/DEMUX
SAMPLE RAM
AEN IO MASKING
ISA AND RASPBERRY PI PICO
RESET CIRCUIT
I/OCHRDY OPEN DRAIN
74LVCxx LOGIC PWR

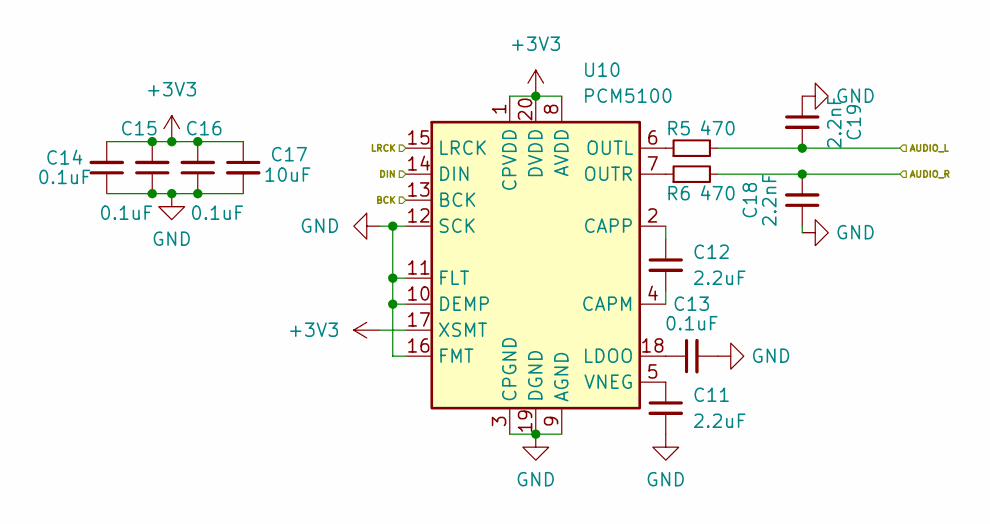
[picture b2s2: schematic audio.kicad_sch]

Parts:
C11, C12: 2.2uF; C_0402_1005Metric
C13, C14, C15, C16: 0.1uF; C_0402_1005Metric
C17: 10uF; C_0603_1608Metric
C18, C19: 2.2nF; C_0402_1005Metric
R5, R6: 470; R_0402_1005Metric
U10: PCM5100; TSSOP-20_4.4x6.5mm_P0.65mm

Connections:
/Audio/AUDIO_L: C19.2, R5.2; also elsewhere on the board
/Audio/AUDIO_R: C18.2, R6.2; also elsewhere on the board
BCK: U10.13 (BCK); also elsewhere on the board
DIN: U10.14 (DIN); also elsewhere on the board
GND: C11.2, C13.2, C14.1, C15.1, C16.1, C17.2, C18.1, C19.1, U10.3 (CPGND), U10.9 (AGND), U10.10 (DEMP), U10.11 (FLT), U10.12 (SCK), U10.16 (FMT), U10.19 (DGND); also elsewhere on the board
LRCK: U10.15 (LRCK); also elsewhere on the board
unnamed: C12.2, U10.4 (CAPM)
unnamed: C12.1, U10.2 (CAPP)
unnamed: C13.1, U10.18 (LDOO)
unnamed: R5.1, U10.6 (OUTL)
unnamed: R6.1, U10.7 (OUTR)
unnamed: C11.1, U10.5 (VNEG)

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

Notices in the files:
sw/isa_analyzer.cpp:
Copyright (C) 2025 Ian Scott
This program is free software; you can redistribute it and/or modify
it under the terms of the GNU General Public License as published by
the Free Software Foundation; either version 2 of the License, or
(at your option) any later version.
hw-chipdown/PicoGUS chipdown.kicad_pcb:
licensed under CERN-OHL-P v2
v2.0 © 2023 Ian Scott aka polpo
hw-hand386/PicoGUS Hand386.kicad_pcb:
CERN-OHL-P v2
Femto Edition ©2023 Ian Scott
